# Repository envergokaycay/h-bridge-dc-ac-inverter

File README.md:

# Wireless Power Transfer System for Electric Vehicles

> 👇 Below you can see the inverter board and a real-time working demo:

## 📌 Project Summary
This project presents a **wireless power transfer (WPT)** system prototype aimed at demonstrating the basic principles of resonant inductive coupling for electric vehicle (EV) charging applications. The prototype is based on an **Arduino-controlled** system that generates a high-frequency AC output using a **H-bridge inverter**, optimized for energy transfer over short distances via an air-core coil pair.

This project was developed as a senior design (bitirme) project in the Electrical and Electronics Engineering Department.

---

## ⚙️ Technical Features

- **Input Voltage:** 24V DC
- **Output Voltage:** ~18V AC (square wave, measured ≈3V AC RMS on multimeter) 
- **Control:** Arduino Uno R3-based PWM generation
- **Topology:** H-Bridge Inverter using IRFZ44N MOSFETs and IR2110 Gate Drivers
- **Regulation:** LM2596 Buck Converter for voltage stepping
- **Rectification:** Fast recovery Schottky diodes at receiver side
- **PCB Design Software:** KiCad 9.0

---

## 🔧 Hardware and Software Used

- **Microcontroller:** Arduino Uno R3  
- **H-Bridge Topology:** Implemented using IRFZ44N MOSFETs  
- **Gate Driver:** IR2110  
- **DC-DC Regulator:** LM2596 (Used to step down the 24V input to 12V to power the IR2110 gate driver ICs. Additionally, another LM2596 module was configured to provide a 5V regulated output to safely interface the Arduino Uno R3’s PWM control signals with the IR2110 inputs.)  
- **Protection Diodes:** 1N5817 Schottky Diodes  
- **PCB Design:** KiCad 9.0 (schematic and PCB design)

---

## ⚙️ PCB Production

The PCB for the inverter stage was fully fabricated by hand, using personal resources and without relying on any professional PCB manufacturing service. The entire process — including etching, manual drilling, and component soldering — was carried out with basic tools, showcasing a hands-on, resourceful approach to hardware prototyping under limited conditions.

---

## 🧪 Testing and Results

- Square wave signal confirmed on the output using an oscilloscope  
- Successful power transfer to receiver coil  
- 3D visualization used for mechanical validation

---

## 📂 Suggested Folder Structure

- `DC-AC Inverter with H-Bridge/`  
  ├── `Code/`  
  ├── `Images and Presentation/`  
    ├── [Operating.mp4](https://www.youtube.com/shorts/zgLSwQ5zg5Q)  
    └── [Wireless Electric Vehicle Charging System KTU EEE.mp4](https://www.youtube.com/shorts/1_IPSUS-X5c)  
  ├── `PCB/`  
    ├── `3D/`  
    ├── `BOM/`  
    ├── `Drill/`  
    └── `Gerber/`  
  ├── `Schematics/`  
  ├── `Simulation Graphs/`  
  └── `README.md`

---

## 📝 Notes

- This circuit is part of a larger system intended to provide an efficient power transfer layer for wireless charging of electric vehicles.  
- All components were selected based on reliable datasheet references and added to KiCad libraries accordingly.

---

## 📚 Future Improvements

- Implement closed-loop current control via feedback
- Design custom receiver coil enclosure
- Replace Arduino with STM32 for better signal precision
- Improve EMI shielding and cooling

---

## 📬 Contact

If you have any questions or want to collaborate, feel free to reach out via GitHub or [LinkedIn](https://www.linkedin.com/in/envergokaycay/).

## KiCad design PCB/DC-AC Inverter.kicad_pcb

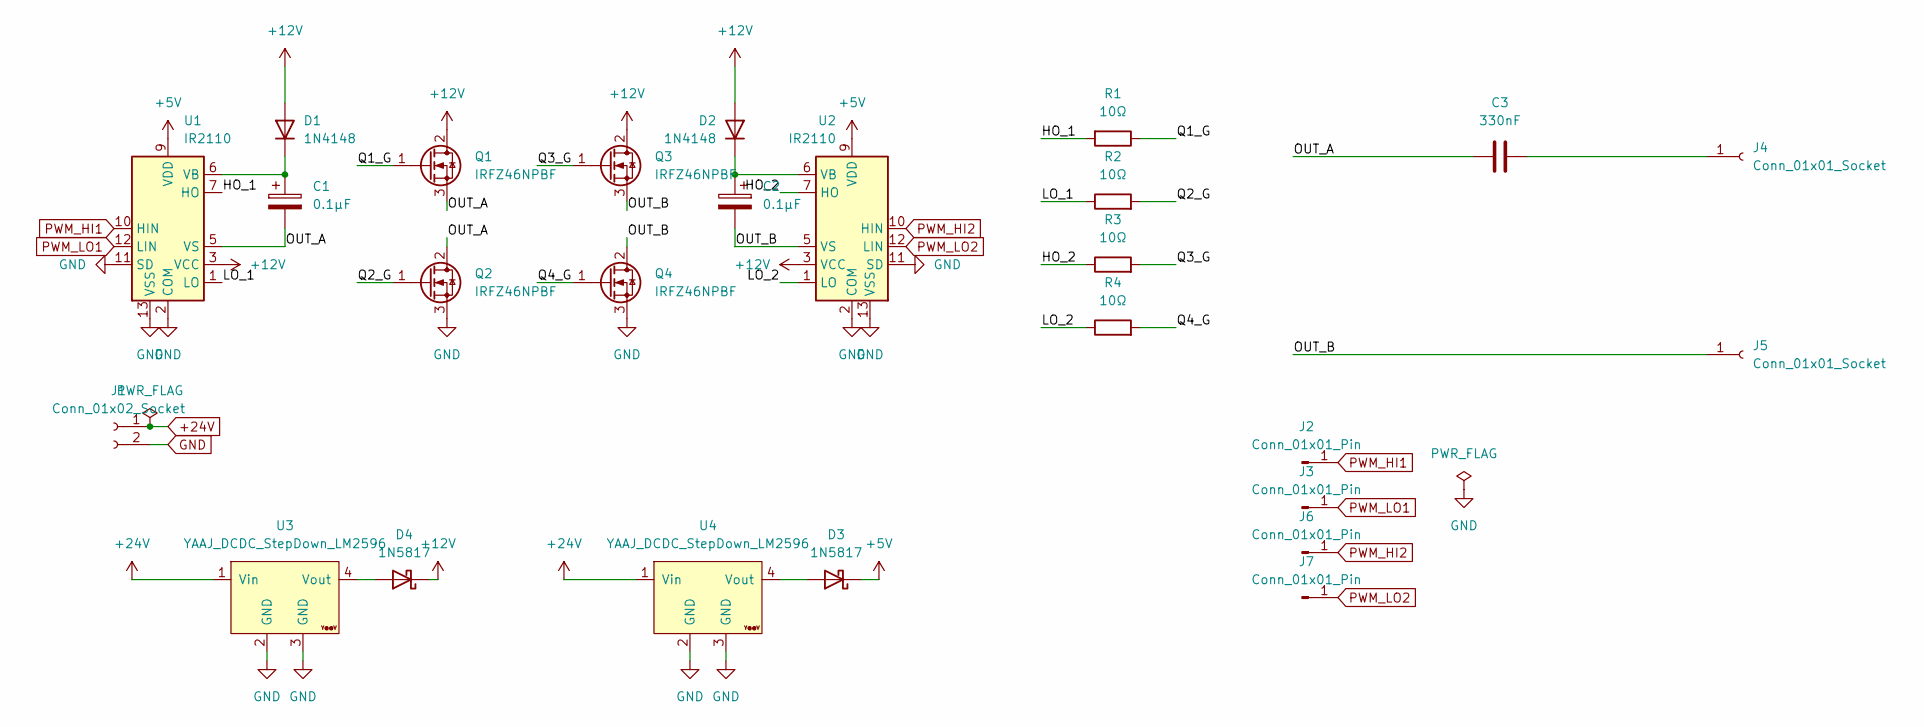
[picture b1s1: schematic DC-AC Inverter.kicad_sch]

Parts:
C1, C2: 0.1µF; R_Axial_DIN0207_L6.3mm_D2.5mm_P7.62mm_Horizontal
C3: 330nF; R_Axial_DIN0207_L6.3mm_D2.5mm_P7.62mm_Horizontal
D1, D2: 1N4148; D_DO-35_SOD27_P7.62mm_Horizontal
D3, D4: 1N5817; D_DO-41_SOD81_P10.16mm_Horizontal
J1: Conn_01x02_Socket; PinHeader_1x02_P2.54mm_Vertical
J2, J3, J6, J7: Conn_01x01_Pin; PinHeader_1x01_P2.54mm_Vertical
J4, J5: Conn_01x01_Socket; PinHeader_1x01_P2.54mm_Vertical
Q1, Q2, Q3, Q4: IRFZ46NPBF; TO-220-3_Vertical
R1, R2, R3, R4: 10Ω; R_Axial_DIN0207_L6.3mm_D2.5mm_P7.62mm_Horizontal
U1, U2: IR2110; DIP-14_W7.62mm
U3, U4: YAAJ_DCDC_StepDown_LM2596

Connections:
+5V: D3.1 (K), U1.9 (VDD), U2.9 (VDD)
+12V: D1.2 (A), D2.2 (A), D4.1 (K), Q1.2 (D), Q3.2 (D), U1.3 (VCC), U2.3 (VCC)
+24V: J1.1, U3.1 (Vin), U4.1 (Vin)
/HO_1: R1.2, U1.7 (HO)
/HO_2: R3.1, U2.7 (HO)
/LO_1: R2.1, U1.1 (LO)
/LO_2: R4.1, U2.1 (LO)
/OUT_A: C1.2, C3.1, Q1.3 (S), Q2.2 (D), U1.5 (VS)
/OUT_B: C2.2, J5.1, Q3.3 (S), Q4.2 (D), U2.5 (VS)
/Q1_G: Q1.1 (G), R1.1
/Q2_G: Q2.1 (G), R2.2
/Q3_G: Q3.1 (G), R3.2
/Q4_G: Q4.1 (G), R4.2
GND: J1.2, Q2.3 (S), Q4.3 (S), U1.2 (COM), U1.11 (SD), U1.13 (VSS), U2.2 (COM), U2.11 (SD), U2.13 (VSS), U3.2 (GND), U3.3 (GND), U4.2 (GND), U4.3 (GND)
unnamed: C1.1, D1.1 (K), U1.6 (VB)
unnamed: C2.1, D2.1 (K), U2.6 (VB)
unnamed: D3.2 (A), U4.4 (Vout)
unnamed: D4.2 (A), U3.4 (Vout)
unnamed: C3.2, J4.1
PWM_HI1: J2.1, U1.10 (HIN)
PWM_HI2: J6.1, U2.10 (HIN)
PWM_LO1: J3.1, U1.12 (LIN)
PWM_LO2: J7.1, U2.12 (LIN)

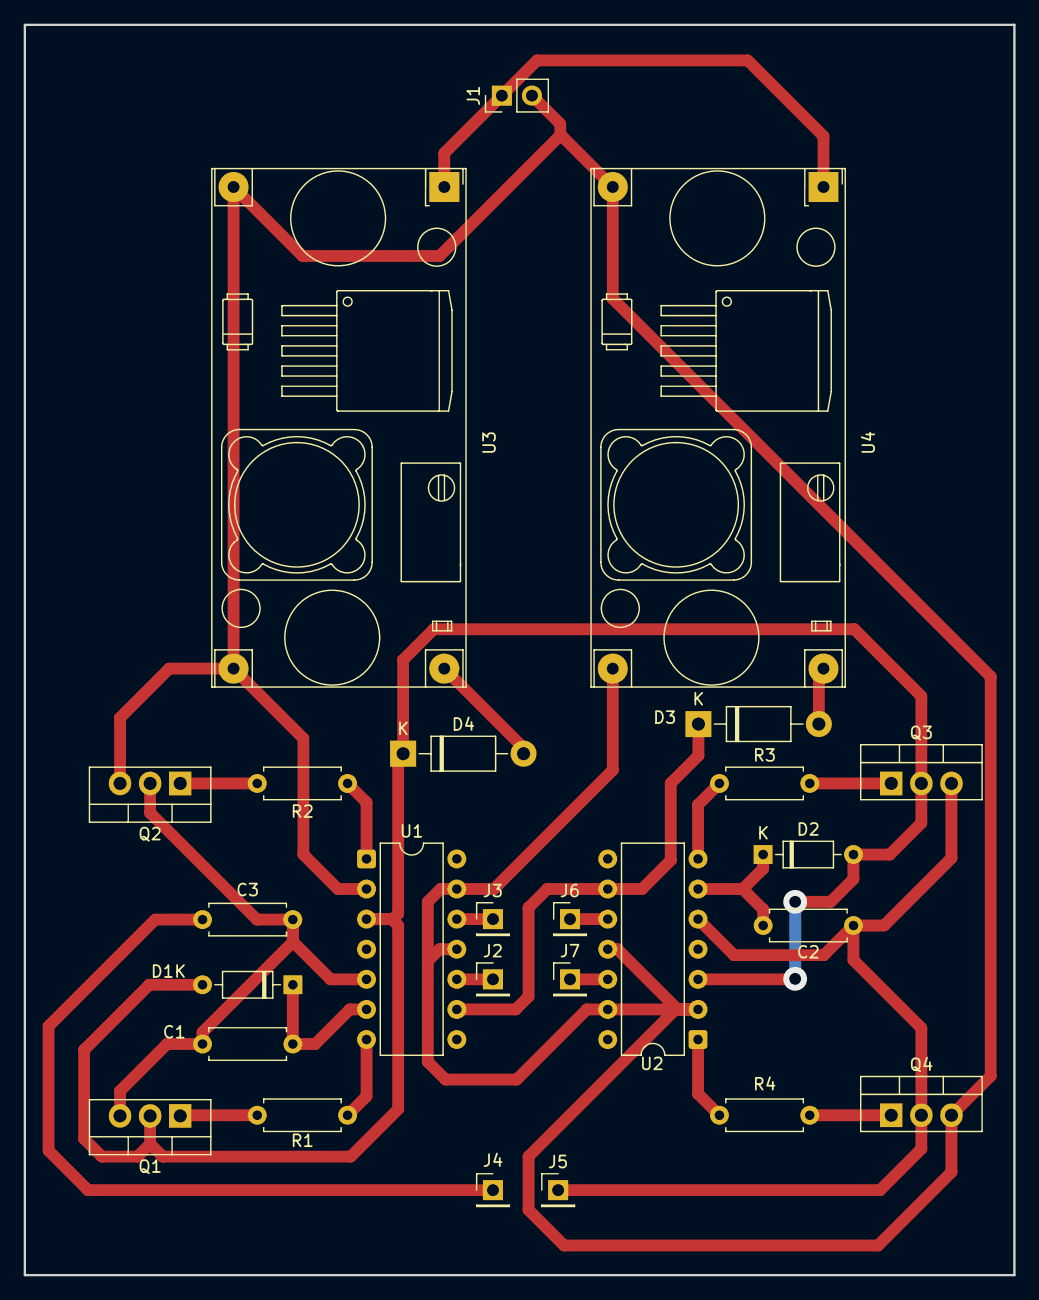
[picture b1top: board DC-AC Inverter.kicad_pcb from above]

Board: 2 copper layers, 83.5 x 105.5 mm, 26 parts (0 on the bottom side), 23 nets.

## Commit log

2025-07-17 Initial commit: Project files and structure added
2025-07-17 Fix folder structure formatting
2025-07-17 Fix: Correct folder structure formatting in README
